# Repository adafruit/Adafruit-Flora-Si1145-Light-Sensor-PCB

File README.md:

## Adafruit Flora Si1145 Light Sensor PCB
<a href="http://www.adafruit.com/products/1981"><br/>
Click here to purchase one from the Adafruit shop</a>

Your wearable can now keep you from getting sunburnt, with the Flora digital UV index sensor. We took our popular SI1145 UV index sensor and cut out everything you don't need for using with our wearable platforms: Flora and Gemma M0. It's small, round, and connects to the I2C bus pads. Flora and Gemma M0 can even use our library code to get calibrated light level and UV index data from the sensor.

Please note: this sensor can be used by <a href="https://www.adafruit.com/product/659">Flora</a> and <a href="https://www.adafruit.com/product/3501">Gemma M0</a> but is too complex for <a href="https://www.adafruit.com/product/1222">Gemma v2 (ATtiny85)</a>!

PCB files for the Adafruit Flora Si1145 Light Sensor. The format is EagleCAD schematic and board layout
- https://www.adafruit.com/product/1981

### License

Adafruit invests time and resources providing this open source design, please support Adafruit and open-source hardware by purchasing products from [Adafruit](https://www.adafruit.com)!

All text above must be included in any redistribution

Designed by Limor Fried/Ladyada for Adafruit Industries.
Creative Commons Attribution/Share-Alike, all text above must be included in any redistribution. 
See license.txt for additional information.

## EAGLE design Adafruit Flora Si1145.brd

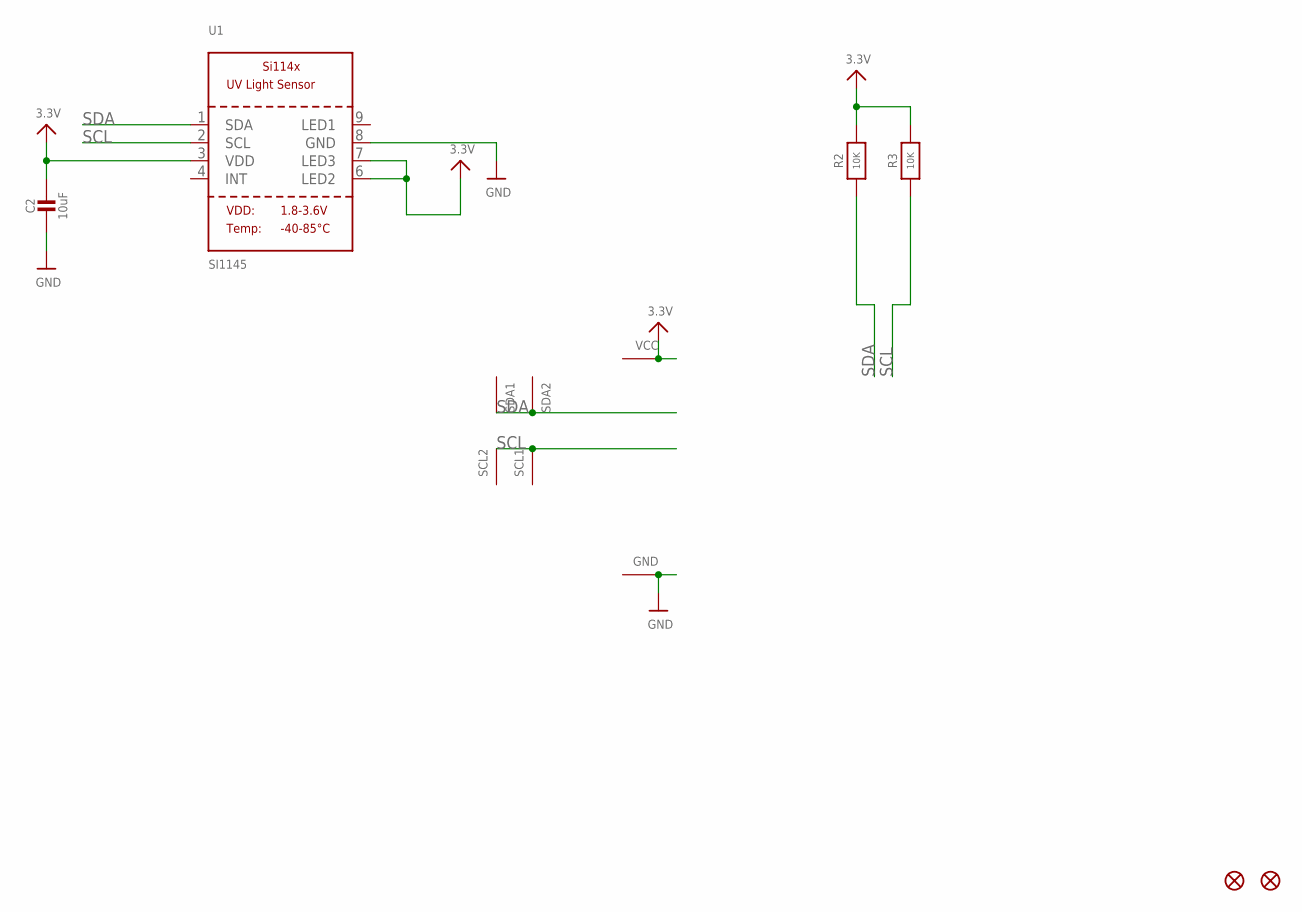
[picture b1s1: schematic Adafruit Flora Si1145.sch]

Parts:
C2: 10uF; 0805-NO
FID1, FID2: FIDUCIAL""; FIDUCIAL_1MM
GND: SEWTAP0.5IN; SEWINGTAP_0.5
R2, R3: 10K; 0805-NO
SCL1, SCL2: SEWTAP0.5IN; SEWINGTAP_0.5
SDA1, SDA2: SEWTAP0.5IN; SEWINGTAP_0.5
U1: SI1145; SI114X
VCC: SEWTAP0.5IN; SEWINGTAP_0.5

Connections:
3.3V: C2.1, R2.2, R3.2, U1.3 (VDD), U1.6 (LED2), U1.7 (LED3), VCC.TAP
GND: C2.2, GND.TAP, U1.8 (GND)
SCL: R3.1, SCL1.TAP, SCL2.TAP, U1.2 (SCL)
SDA: R2.1, SDA1.TAP, SDA2.TAP, U1.1 (SDA)

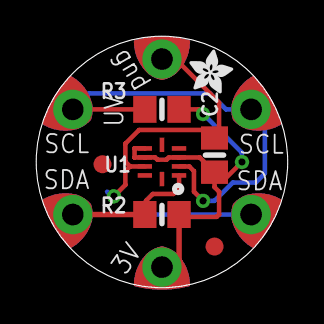
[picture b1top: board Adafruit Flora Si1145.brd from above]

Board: 2 copper layers, 14.0 x 14.0 mm, 14 parts (1 on the bottom side), 4 nets.

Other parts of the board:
U$3, U$4: ADAFRUIT_2.5MM

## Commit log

2016-08-17 init
2022-06-26 Added mention of sensor being compatible with Gemma M0
    This will keep new readers and makers up to date about what one can use with this sensor.
    Provided also links for Gemma M0 and Gemma v2 to Adafruit online store.

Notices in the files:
parts and their libraries:
microbuilder: This work is placed in the public domain, and may be freely used for commercial and non-commercial work with the following conditions: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
